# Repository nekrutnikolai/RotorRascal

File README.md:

For the build guide, documentation, and more, please check out our [Wiki page](https://github.com/cornellmotionstudio/JacksonDronev2/wiki).

# Getting Started

Clone the project
```
git clone https://github.com/nekrutnikolai/RotorRascal.git
```

Go to the software dir.
```
cd RotorRascal && cd software
```

Build the project

```
./builder
```

## Final Report Components

### Project Introduction
- One sentence "sound bite" that describes your project.
    We built and implemented PID control on a Pico-powered quadcopter to hover on a gimbal stand with throttle input from a controller. 

- A summary of what you did and why.

### High level design

- Rationale and sources of your project idea
    Bryan, Martin and I enjoy drones and quadcopters, we thought it would be a neat idea to develop a somewhat functioning flight controller to control the drone with an onboard IMU for orientation data, an external remote to set the throttle position, and an electronic speed controller (ESC). 
    
    Nikolai is a part of the Motion Studio "Drone Squad" advised by Dr. Beatriz Asfora which was involved in the creating of this final project idea. Out of the Drone Squad there was already a prototype developed by Deemo Chen with a PCB integrating an IMU and Pi Pico along with a skeleton of code on how to control each PWM ESC channel.

    The long-term objective of this project is to support the integration of these Pico-based drones made from 3D printed components into ECE and MAE courses. For instance, these drones could be integrated in the ECE microcontrollers curriculum and the students could work on code developing/tuning a PID controller. Or, for a MAE dynamics course, the students could use these drones for dynamics modelling.

- background math

    The effects of a $P$, $I$ and $D$ terms are well know. If we think of controlling the mass in a spring-mass-dashpot system, the $P$ term acts like increasing the stiffness of the spring, whereas the $D$ term effectively adds damping to the system. An $I$ term in general achieves the desirable porperty of having zero steady state. 

    Even though our system is not a spring-mass-dashpot system, we can still keep in mind the above intuitive properties of each of the three terms of a PID controller. 
    
    We ended up using the same set of three $P$, $I$, $D$ coefficients for controlling the pitch and the roll angle, and a different set of three $P$, $I$, $D$ coefficients for the yaw angle. Therefore, $6$ in total.

    We did not do any modelling of the drone ("plant") dynamics, and did the tuning by trial and error. With more time, we would obtain the quations of motion and linearize about the desired hover position. We would get a linear set of equations, keeping in mind that we should include . There would be two approaches: either design the controller using the state-space approach, or frequency design. 
    
    If we chose the state-space approach, 

- logical structure
    1. Initialize radio and sensors
    2. Calibrate ESCs and Gyro
    3. Initialize serial PID tuning interface
    4. Wait for arm signal from controller
        1. Erase all store PID values -- effectively reset controls
    5. Spin up motors to minimum throttle and begin executing PID loop
    6. Continue executing PID loop until disarm

- hardware/software tradeoffs
    **PID loop speed:** Since the drone is a complicated, unstable system with 4 motors and 6 degrees of freedom, it is vital to have a fast control loop. From our testing and with lab 3, we found a value of 1kHz to work well. Compared to lab 3, we need to be computing the PID terms for 3 axes as opposed to a single PID axis. Those three axes are pitch, roll, and yaw. Pitch and roll have the same PID parameters and yaw has different PID parameters that will be discussed later in this section. 

    **Pico W:** The Pico W was used to allow future expansion of wireless capabilites. Future work could involve developing a web server that hosts an interactive PID tuning interface where students in courses could drag sliders and visualize the gyro output and controller output to see the performance of the PID developed or the drone modelled.

    **Controlling 4 Motors:** The PWM needs to be computed for each of the 4 motors, as opposed to a single axis like in lab 3, which takes more time to compute. This point is combined with the previous point made above, leading to significantly more computation involved. Essentially, 6 (PID terms) x 3 (axes) x 4 (motors) = 64 times the amount of computation relative to lab 3 since that lab had 1 axis and 1 motor. Additionally, changing the motor output has effects on the physical system, where changing the motor speed induces a torque on the drone, affecting the yaw axis, which will be discussed in the next section.

    **Yaw Compensation:** Since the drone is a physical system, we had to take into account physics for our software development and development. The quick and dirty solution that we came up with was having different PID weights for the yaw axis as opposed to the pitch and roll axes. For instance, the D term had to be greatly reduced as so the yaw compensation would not fight the other axes and enter an unstable jittery mess.

    **Long-Term Gyro Drift:** Gyro drift could have an effect on the longer-term characteristics in the minute to hour timescales. This is not much of a concern, however, as the drone only has battery life for 5 minutes at most due to the extreme power draw of flight. We implemented the gyro to calibrate everytime a battery is plugged in, so setting 

- Discuss existing patents, copyrights, and trademarks which are relevant to your project.
    There are no existing patents, copyrights, and trademarks which are relevant to our project.

### Program/hardware design
- program details. What parts were tricky to write?
    The skeleton of code we started from was unnecessarily complicated, so our biggest challenge was discovering how the actual control algorithms and peripheral interfaces were implemented. The code for the radio interface was reverse-engineered based on the serial string received from the controller. Although that was straightforward, it was far less straightforward to implement pitch, roll, and yaw control from the controller to the rest of the code. Hence, we stuck with throttle and arm only. From there, we scrapped his PID control as it was unfinished and did not work and wrote our own. This has its own challenges as we are implementing it on a quadcopter with four motors. One really important thing that we realized early was that the physical model for how yaw is controlled is extremely different from how pitch and roll is controlled. This means we needed separate coefficients for yaw PID and pitch/roll PID. To implement this, we simply compute the PID values, then apply the coefficients separately in the motor mixing calculations. 
  
- Hardware details -- Could someone else build this based on what you have written?

> Insert image of labelled diagram showcasing components

Since drones out of the same parts 

    - Make this into a build guide!
    - This is already developed
    - Add bill of materials

Table 1: Drone components (UPDATE)

| **Component**         | **Part Description**                                        | **Estimated Price**     |
|------------------------|-------------------------------------------------------------|--------------------------|
| **Frame**              | 5" carbon fiber frame for freestyle or racing              | $30–$70                  |
| **Motors**             | 2207 or 2306 brushless motors, 1700–2500KV                 | $15–$30 each             |
| **ESC (4-in-1)**       | 4-in-1 ESC, 30–60A, DShot600 support                        | $40–$80                  |
| **Propellers**         | 5" tri-blade props (e.g., 5x4.3x3)                          | $3–$6 per set            |
| **Radio Receiver (Rx)**| ELRS, Crossfire, or FrSky protocol receiver                | $15–$30                  |
| **Battery**            | 4S or 6S LiPo, 1300–1800mAh                                 | $25–$50                  |
| **Transmitter (Tx)**   | RC controller (e.g., Radiomaster, Tango 2)                 | $100–$250                |

Table 2: Drone accessories (UPDATE)

| **Component**         | **Part Description**                                        | **Estimated Price**     |
|------------------------|-------------------------------------------------------------|--------------------------|
| **Transmitter (Tx)**   | RC controller (e.g., Radiomaster TX16S, TBS Tango 2)       | $100–$250                |
| **Battery Charger**    | LiPo balance charger (AC/DC or DC only)                    | $40–$100                 |
| **Batteries**          | 4S or 6S LiPo, 1300–1800mAh, for flight power              | $25–$50 each             |

- Be sure to specifically reference any design or code you used from someone else.
    
    We referenced the design and code found at the following repository: https://github.com/cornellmotionstudio/JacksonDronev2

### Tuning the drone PID's
Tuning the PIDs on a quadcopter is not the easiest task when it comes to a PID loop that you wrote yourself, on hardware that you also built yourself. It's especially difficult because there is no advice from other people that have experienced the issues. It boils down to a raw understanding of the physical model and the code at play. With our particular situation, the most difficult thing was trying to understand what was due to the gyro or if the issues were being caused by dynamics between the pitch and roll competing with yaw correction. Due to the physical model of a quadcopter, if a correction is made to any motor, it affects yaw, therefore inducing a yaw error that requires correction. Finding a starting point that did not have an oscillatory loop between the pitch/roll axis and the yaw axis was a challenge, but in the end, we were able to find a good starting point PIDs.

| Axis        | Kp  | Ki   | Kd    |
|-------------|-----|------|-------|
| Roll/Pitch  | 4.5 | 0.4  | 0.08  |
| Yaw         | 3.0 | 0.25 | 0.015 |

Continuing with our tuning, we were able to find really good PID values that resulted in an ability to react really well to outside stimuli, hold level quite well, and correct for new changes in center of gravity on the drone. The biggest challenge is finding a set of PIDs that works well through the whole throttle range; however, though this should not be the case unless we are amplifying noise or vibration caused by different throttle positions in our accelerometer measurements. Something we did still experience regardless of the amount of tuning done was a continuous angle error that varied with time; it almost appeared to be steady-state error that would then be corrected by the I term, which led us down some tuning rabbit holes in attempts to fix it. However, we believe now that it is actually drift occurring through our complimentary filter, and given more time, I believe we would have been able to correct this issue. Coming to this conclusion was based on testing with a solid offset that would need to be corrected by the I term, which did occur and namely occurred much faster than the correction to this drift. Additionally, testing our P term by tapping different points to induce an angle error and observing how quickly the drone corrected these errors indicated that whatever this drift was, it was being ignored by the PID loop. Testing PIDs was done purely on a custom-designed stand designed by Nikolai. The stand allows the drone to move along the pitch, roll, yaw, and vertical axis. Meaning we can simulate a cover that is restricted in translational movement. Using this stand with a power cable and a USB cable dangling from opposite ends of the drone, we are able to safely test indoors despite the high chance of unstable flight. 

### Results of the design
- Any and all test data, scope traces, waveforms, etc
- speed of execution (hesitation, filcker, interactiveness, concurrency)
- accuracy (numeric, music frequencies, video signal timing, etc)
- how you enforced safety in the design.
- usability by you and other people

### Conclusions
- Analyse your design in terms of how the results met your expectations. What might you do differently next time?
    Got it working pretty well but it seems almost that we could have gotten it working better perhaps?
- How did your design conform to the applicable standards?
- Intellectual property considerations.
    - Did you reuse code or someone else's design? Did you use any of Altera's IP?
    - Did you use code in the public domain?
    - Are you reverse-engineering a design? How did you deal with patent/trademark issues?
    - Did you have to sign non-disclosure to get a sample part?
    - Are there patent opportunites for your project?

### Appendix A (permissions)

The group **approves** this report for inclusion on the course website.

The group **approves** the video for inclusion on the course youtube channel.

### Additional appendices
- Appendix with commented Verilog and/or program listings.
- Appendix with schematics if you build hardware external to the DE1-SoC board (you can download free software from expresspcb.com to draw schematics).
- Appendix with a list of the specific tasks in the project carried out by each team member.
- References you used:
    - Data sheets
    - Vendor sites
    - Code/designs borrowed from others
    - Background sites/paper

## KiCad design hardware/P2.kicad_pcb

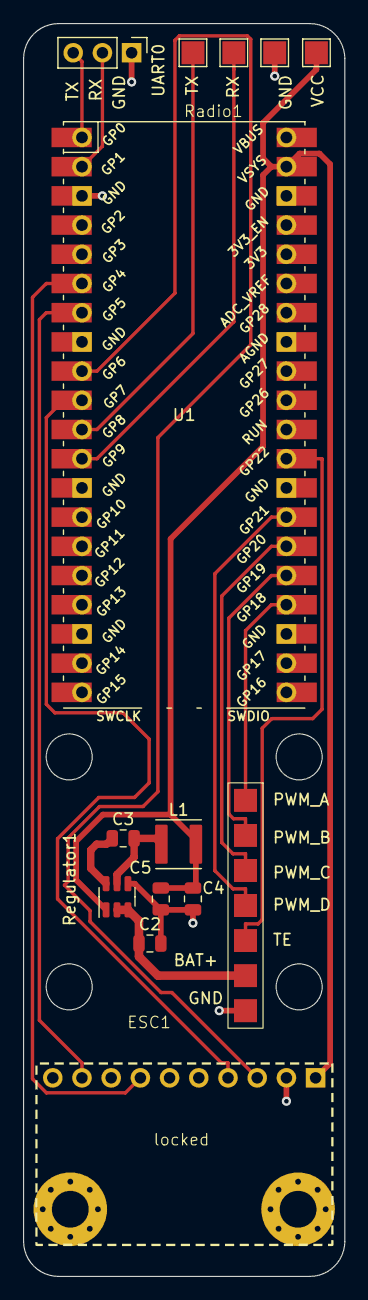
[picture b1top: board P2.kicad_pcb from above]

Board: 2 copper layers, 27.9 x 109.0 mm, 17 parts (0 on the bottom side), 18 nets.

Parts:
C2: 10uF; C_0805_2012Metric
C3: 0.1uF; C_0805_2012Metric
C4, C5: 22uF; C_0805_2012Metric
ESC1: ESC
H1, H2, H3, H4: MountingHole; MountingHole_4mm
H5, H6: MountingHole; MountingHole_3.2mm_M3_Pad_Via
L1: 4.7uH; L_Abracon_ASPI-4030S
Radio1: Radio
Regulator1: AP63203WU; TSOT-23-6
U1: Pico; RPi_Pico_SMD_TH
UART0: UART; PinHeader_1x03_P2.54mm_Vertical
locked: MPU9250-Breakout

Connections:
+3V3: C4.1, C5.1, L1.2, Radio1.1 (VCC), Regulator1.1 (FB), U1.39 (VSYS), locked.1 (VCC)
+BATT: C2.1, ESC1.5 (BAT+), Regulator1.2 (EN), Regulator1.3 (IN)
/CS: U1.7 (GPIO5), locked.9 (NCS)
/MISO: U1.6 (GPIO4), locked.7 (ADO)
/MOSI: U1.10 (GPIO7), locked.4 (SDA)
/PWM_A: ESC1.1 (PWM_A), U1.24 (GPIO18)
/PWM_B: ESC1.2 (PWM_B), U1.25 (GPIO19)
/PWM_C: ESC1.3 (PWM_C), U1.26 (GPIO20)
/PWM_D: ESC1.4 (PWM_D), U1.27 (GPIO21)
/RX: Radio1.3 (TX), U1.12 (GPIO9)
/SCK: U1.9 (GPIO6), locked.3 (SCL)
/TE: ESC1.6 (TE), U1.29 (GPIO22)
/TX: Radio1.4 (RX), U1.11 (GPIO8)
GND: C2.2, C4.2, C5.2, ESC1.7 (GND), Radio1.2 (GND), Regulator1.4 (GND), U1.3 (GND), UART0.1, locked.2 (GND)
unnamed: U1.2 (GPIO1), UART0.2
unnamed: U1.1 (GPIO0), UART0.3
unnamed: C3.1, Regulator1.6 (BST)
unnamed: C3.2, L1.1, Regulator1.5 (SW)

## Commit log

2024-07-29 Jackson Wiki for Edits
2024-07-29 figures new
2025-04-21 added latest code
2025-04-25 got PID working
2025-04-25 added serial PID tuning capability
2025-04-28 added yaw tuning
2025-04-30 fixed yaw directions, added controller accumulation, etc
2025-05-01 FINAL PUSH
2025-05-05 starting website work
2025-05-05 fixed issues
2025-05-05 changing size
2025-05-05 added project reqs
2025-05-05 added bullet points
2025-05-05 testing latex functionality
2025-05-05 progress check
2025-05-05 image testing
2025-05-05 progress update
2025-05-05 jpeg to jpg
2025-05-05 wrapping up with latest changes
2025-05-05 added transparency agreements
2025-05-05 fixed images
2025-05-06 adding tables
2025-05-06 minor changes
2025-05-08 Update README.md
    Filled in tuning PIDs section
2025-05-09 Update README.md
    Added starting PID values
2025-05-09 finalizing readme
2025-05-09 Website upload
2025-05-16 finalized site
2025-05-16 forgot to save it seems lol
2025-05-16 slight stylistic things
2025-05-16 embedded drone image
2025-05-16 fixed banner
2025-05-16 messin around
